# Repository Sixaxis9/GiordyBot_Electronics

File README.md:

# CNC-3Dprinter

In this repository I have uploaded all the material related to a fresh design of a machine capable of working various type of materials, including wood and aluminum, with the nice addition of an extruder to use it as a 3D printer.

I have uploaded the Eagle project of the board. Below you can find a list of all the important feautures and the distinctive sign of this board. I also have uploaded the Gerber files for printing a PCB, in case you would like to power your 3D printer or CNC with my hardware.

I also made a complete CAD model of this build, complete with FEM analysis in order to pick the best materials and optimize dimensions of the design. I will upload all those files in the nearest future.

A Wiki is available in the [apposite section](https://github.com/Sixaxis9/CNC-3Dprinter/wiki)

Below some pictures of the board:

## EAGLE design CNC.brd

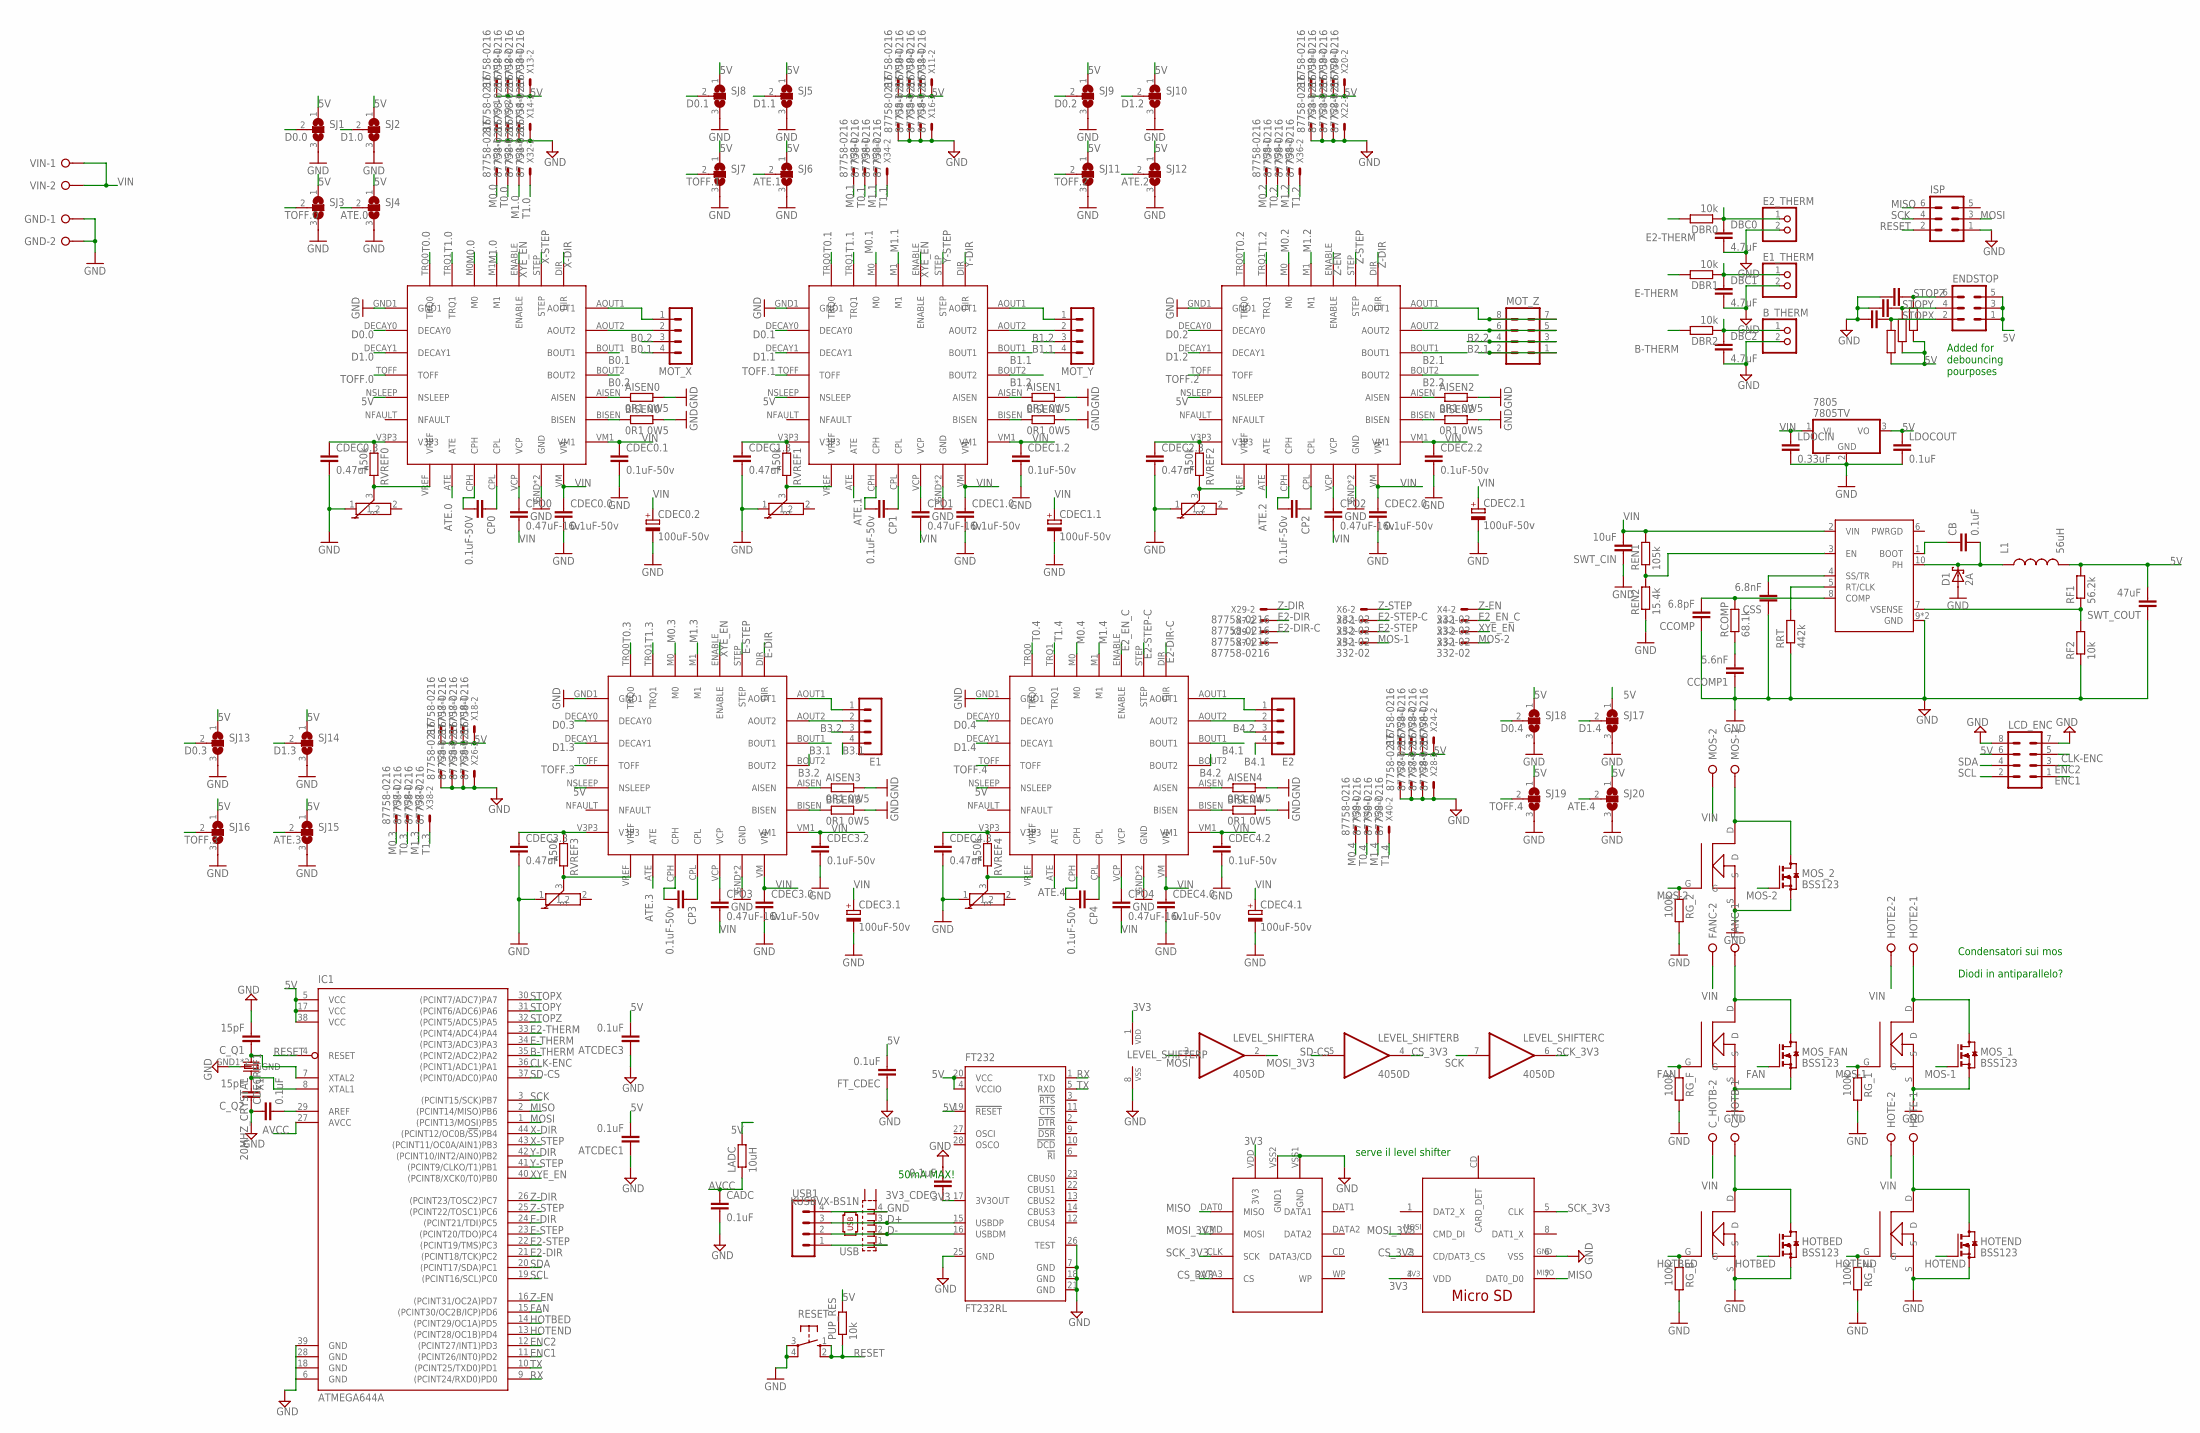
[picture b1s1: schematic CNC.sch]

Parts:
3V3_CDEC: 0.1uF; C0603
7805: 7805TV; TO220V
AISEN0, AISEN1, AISEN2, AISEN3, AISEN4: 0R1 0W5; R0805
ATCDEC1, ATCDEC3: 0.1uF; C0603
BISEN0, BISEN1, BISEN2, BISEN3, BISEN4: 0R1 0W5; R0805
B_THERM: PINHD-1X2; 1X02
CADC: 0.1uF; C0603
CB: 0.1uF; C0603
CCOMP: 6.8pF; C0603
CCOMP1: 5.6nF; C0603
CDEC0.0, CDEC0.1, CDEC1.0, CDEC1.2, CDEC2.0, CDEC2.2, CDEC3.0, CDEC3.2, CDEC4.0, CDEC4.2: 0.1uF-50v; C0603
CDEC0.2, CDEC1.1, CDEC2.1, CDEC3.1, CDEC4.1: 100uF-50v; E3,5-8
CDEC0.3, CDEC1.3, CDEC2.3, CDEC3.3, CDEC4.3: 0.47uF; C0603
CDECREF1: 0.1uF; C0603
CP0: 0.1uF-50V; C0603
CP1, CP2, CP3, CP4: 0.1uF-50v; C0603
CPO0, CPO1, CPO2, CPO3, CPO4: 0.47uF-16v; C0603
CSS: 6.8nF; C0603
C_HOTB: W237-02P; W237-132
C_Q1, C_Q2: 15pF; C0603
D1: 2A; SMB
DBC0, DBC1, DBC2: 4.7uF; C0603
DBC3, DBC4, DBC5: 0.1uF; C0603
DBR0, DBR1, DBR2, DBR3, DBR4, DBR5: 10k; R0603
E1, E2: MA04-1
E1_THERM, E2_THERM: PINHD-1X2; 1X02
ENDSTOP: MA03-2
EXT_1, EXT_2: DRV8880; HTSSOP
FANC: W237-02P; W237-132
FT232: FT232RL; SSOP28
FT_CDEC: 0.1uF; C0603
GND: W237-02P; W237-132
HOTBED: BSS123; SOT23
HOTBED1: POWER_MOSFET; D2PAK
HOTE, HOTE2: W237-02P; W237-132
HOTEND: BSS123; SOT23
HOTEND1: POWER_MOSFET; D2PAK
IC1: ATMEGA644A; TQFP44
ISP: MA03-2
L1: 56uH; INDUCTOR
LADC: 10uH; R0603
LCD_ENC: MA04-2
LDOCIN: 0.33uF; C0603
LDOCOUT: 0.1uF; C0603
LEVEL_SHIFTER: 4050D; SO16
MOS: W237-02P; W237-132
MOS11, MOS22: POWER_MOSFET; D2PAK
MOS_1, MOS_2: BSS123; SOT23
MOS_FAN: BSS123; SOT23
MOS_FAN1: POWER_MOSFET; D2PAK
MOT_X: MA04-1
MOT_Y: MA04-1
MOT_Z: MA04-2
PUP_RES: 10k; R0603
RCOMP: 68.1k; R0603
REN1: 105k; R0603
REN2: 15.4k; R0603
RESET: 10-XX; B3F-10XX
RF1: 56.2k; R0603
RF2: 10k; R0603
RG_1, RG_2: 100k; R0603
RG_B: 100k; R0603
RG_E: 100k; R0603
RG_F: 100k; R0603
RRT: 442k; R0603
RVREF0, RVREF1, RVREF2, RVREF3, RVREF4: 150k; R0603
SD: SD_CARD
SJ1, SJ2, SJ3, SJ4, SJ5, SJ6, SJ7, SJ8, SJ9, SJ10, SJ11, SJ12, SJ13, SJ14, SJ15, SJ16, SJ17, SJ18, SJ19, SJ20: SJ2W; SJ_2
SUPPLY: TPS54160; MSOP
SWT_CIN: 10uF; C0603
SWT_COUT: 47uF; C0603
T0: 100k; TRIMMER
T1, T2, T3, T4: TRIMMER
USB: KUSBVX-BS1N
USB1: MA04-1
USD: MICRO-SD
VIN: W237-02P; W237-132
X1: 20MHZ_CRYSTAL; SMD-3225_4P
X3, X4, X5, X6: 332-02
X7, X9, X10, X11, X12, X13, X14, X15, X16, X17, X18, X19, X20, X21, X22, X23, X24, X25, X26, X27, X28, X29, X31, X32, X33, X34, X35, X36, X37, X38, X39, X40: 87758-0216
X_AXIS: DRV8880; HTSSOP
Y-AXIS: DRV8880; HTSSOP
Z_AXIS: DRV8880; HTSSOP

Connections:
3V3: 3V3_CDEC.1, FT232.17 (3V3OUT), LEVEL_SHIFTER.1 (VDD), SD.VDD (3V3), USD.4 (VDD)
5V: 7805.3 (VO), ATCDEC1.2, ATCDEC3.2, DBR3.2, DBR4.2, DBR5.2, ENDSTOP.1, ENDSTOP.3, ENDSTOP.5, EXT_1.NSLEEP, EXT_2.NSLEEP, FT232.4 (VCCIO), FT232.19 (!RESET), FT232.20 (VCC), FT_CDEC.2, IC1.5 (VCC), IC1.17 (VCC), IC1.38 (VCC), L1.2, LADC.2, LCD_ENC.6, LDOCOUT.1, PUP_RES.2, RF1.2, SJ1.1, SJ2.1, SJ3.1, SJ4.1, SJ5.1, SJ6.1, SJ7.1, SJ8.1, SJ9.1, SJ10.1, SJ11.1, SJ12.1, SJ13.1, SJ14.1, SJ15.1, SJ16.1, SJ17.1, SJ18.1, SJ19.1, SJ20.1, SWT_COUT.2, X10.1, X10.2, X11.1, X11.2, X12.1, X12.2, X13.1, X13.2, X17.1, X17.2, X18.1, X18.2, X19.1, X19.2, X20.1, X20.2, X23.1, X23.2, X24.1, X24.2, X_AXIS.NSLEEP, Y-AXIS.NSLEEP, Z_AXIS.NSLEEP
ATE.0: SJ4.2, X_AXIS.ATE
ATE.1: SJ6.2, Y-AXIS.ATE
ATE.2: SJ12.2, Z_AXIS.ATE
ATE.3: EXT_1.ATE, SJ15.2
ATE.4: EXT_2.ATE, SJ20.2
AVCC: CADC.1, IC1.27 (AVCC), LADC.1
B0.1: MOT_X.4, X_AXIS.BOUT1
B0.2: MOT_X.3, X_AXIS.BOUT2
B1.1: MOT_Y.4, Y-AXIS.BOUT1
B1.2: MOT_Y.3, Y-AXIS.BOUT2
B2.1: MOT_Z.1, MOT_Z.2, Z_AXIS.BOUT1
B2.2: MOT_Z.3, MOT_Z.4, Z_AXIS.BOUT2
B3.1: E1.4, EXT_1.BOUT1
B3.2: E1.3, EXT_1.BOUT2
B4.1: E2.4, EXT_2.BOUT1
B4.2: E2.3, EXT_2.BOUT2
B-THERM: DBR2.2, IC1.35 ((PCINT2/ADC2)PA2)
CLK-ENC: IC1.36 ((PCINT1/ADC1)PA1), LCD_ENC.5
CS_3V3: LEVEL_SHIFTER.4 (O), SD.DATA3 (CS), USD.2 (CD/DAT3_CS)
D0.0: SJ1.2, X_AXIS.DECAY0
D0.1: SJ8.2, Y-AXIS.DECAY0
D0.2: SJ9.2, Z_AXIS.DECAY0
D0.3: EXT_1.DECAY0, SJ13.2
D0.4: EXT_2.DECAY0, SJ18.2
D1.0: SJ2.2, X_AXIS.DECAY1
D1.1: SJ5.2, Y-AXIS.DECAY1
D1.2: SJ10.2, Z_AXIS.DECAY1
D1.3: EXT_1.DECAY1, SJ14.2
D1.4: EXT_2.DECAY1, SJ17.2
D+: FT232.15 (USBDP), USB.3, USB1.3
D-: FT232.16 (USBDM), USB.2, USB1.2
E2-DIR: IC1.21 ((PCINT18/TCK)PC2), X7.2
E2-DIR-C: EXT_2.DIR, X29.1
E2-STEP: IC1.22 ((PCINT19/TMS)PC3), X5.2
E2-STEP-C: EXT_2.STEP, X6.1
E2-THERM: DBR0.2, IC1.33 ((PCINT4/ADC4)PA4)
E2_EN_C: EXT_2.ENABLE, X4.1
E-DIR: EXT_1.DIR, IC1.24 ((PCINT21/TDI)PC5)
E-STEP: EXT_1.STEP, IC1.23 ((PCINT20/TDO)PC4)
E-THERM: DBR1.2, IC1.34 ((PCINT3/ADC3)PA3)
ENC1: IC1.11 ((PCINT26/INT0)PD2), LCD_ENC.1
ENC2: IC1.12 ((PCINT27/INT1)PD3), LCD_ENC.3
FAN: IC1.15 ((PCINT30/OC2B/ICP)PD6), MOS_FAN.1 (G), MOS_FAN1.G, RG_F.1
GND: 3V3_CDEC.2, 7805.2 (GND), AISEN0.2, AISEN1.2, AISEN2.2, AISEN3.2, AISEN4.2, ATCDEC1.1, ATCDEC3.1, BISEN0.2, BISEN1.2, BISEN2.2, BISEN3.2, BISEN4.2, B_THERM.2, CADC.2, CCOMP.1, CCOMP1.1, CDEC0.0.2, CDEC0.1.2, CDEC0.2.-, CDEC0.3.2, CDEC1.0.2, CDEC1.1.-, CDEC1.2.2, CDEC1.3.2, CDEC2.0.2, CDEC2.1.-, CDEC2.2.2, CDEC2.3.2, CDEC3.0.2, CDEC3.1.-, CDEC3.2.2, CDEC3.3.2, CDEC4.0.2, CDEC4.1.-, CDEC4.2.2, CDEC4.3.2, CDECREF1.1, CSS.1, C_Q1.2, C_Q2.1, D1.A, DBC0.2, DBC1.2, DBC2.2, DBC3.2, DBC4.2, DBC5.2, E1_THERM.2, E2_THERM.2, EXT_1.GND, EXT_1.GND1, EXT_1.GND2 (GND), EXT_2.GND, EXT_2.GND1, EXT_2.GND2 (GND), FT232.7 (GND), FT232.18 (GND), FT232.21 (GND), FT232.25 (GND), FT232.26 (TEST), FT_CDEC.1, GND.1, GND.2, HOTBED.2 (S), HOTBED1.S, HOTEND.2 (S), HOTEND1.S, IC1.6 (GND), IC1.18 (GND), IC1.28 (GND), IC1.39 (GND), ISP.1, LCD_ENC.7, LCD_ENC.8, LDOCIN.2, LDOCOUT.2, LEVEL_SHIFTER.8 (VSS), MOS11.S, MOS22.S, MOS_1.2 (S), MOS_2.2 (S), MOS_FAN.2 (S), MOS_FAN1.S, REN2.1, RESET.3, RESET.4 (P1), RF2.1, RG_1.2, RG_2.2, RG_B.2, RG_E.2, RG_F.2, RRT.1, SD.VSS1 (GND), SD.VSS2 (GND1), SJ1.3, SJ2.3, SJ3.3, SJ4.3, SJ5.3, SJ6.3, SJ7.3, SJ8.3, SJ9.3, SJ10.3, SJ11.3, SJ12.3, SJ13.3, SJ14.3, SJ15.3, SJ16.3, SJ17.3, SJ18.3, SJ19.3, SJ20.3, SUPPLY.9 (GND), SUPPLY.GND, SWT_CIN.1, SWT_COUT.1, T0.1, T1.1, T2.1, T3.1, T4.1, USB.4, USB1.4, USD.6 (VSS), X1.GND1 (GND), X1.GND2 (GND), X9.1, X9.2, X14.1, X14.2, X15.1, X15.2, X16.1, X16.2, X21.1, X21.2, X22.1, X22.2, X25.1, X25.2, X26.1, X26.2, X27.1, X27.2, X28.1, X28.2, X_AXIS.GND, X_AXIS.GND1, X_AXIS.GND2 (GND), Y-AXIS.GND, Y-AXIS.GND1, Y-AXIS.GND2 (GND), Z_AXIS.GND, Z_AXIS.GND1, Z_AXIS.GND2 (GND)
HOTBED: HOTBED.1 (G), HOTBED1.G, IC1.14 ((PCINT29/OC1A)PD5), RG_B.1
HOTEND: HOTEND.1 (G), HOTEND1.G, IC1.13 ((PCINT28/OC1B)PD4), RG_E.1
M0.0: X31.1, X_AXIS.M0
M0.1: X33.1, Y-AXIS.M0
M0.2: X35.1, Z_AXIS.M0
M0.3: EXT_1.M0, X37.1
M0.4: EXT_2.M0, X39.1
M1.0: X31.2, X_AXIS.M1
M1.1: X33.2, Y-AXIS.M1
M1.2: X35.2, Z_AXIS.M1
M1.3: EXT_1.M1, X37.2
M1.4: EXT_2.M1, X39.2
MISO: IC1.2 ((PCINT14/MISO)PB6), ISP.6, SD.DAT0 (MISO), USD.7 (DAT0_D0)
MOS-1: MOS11.G, MOS_1.1 (G), RG_1.1, X5.1
MOS-2: MOS22.G, MOS_2.1 (G), RG_2.1, X3.1
MOSI: IC1.1 ((PCINT13/MOSI)PB5), ISP.3, LEVEL_SHIFTER.3 (I)
MOSI_3V3: LEVEL_SHIFTER.2 (O), SD.CMD (MOSI), USD.3 (CMD_DI)
unnamed: DBC1.1, DBR1.1, E1_THERM.1
unnamed: DBC0.1, DBR0.1, E2_THERM.1
unnamed: REN1.1, REN2.2, SUPPLY.3 (EN)
unnamed: USB.1, USB1.1
unnamed: MOT_Y.1, Y-AXIS.AOUT1
unnamed: MOT_Y.2, Y-AXIS.AOUT2
unnamed: MOT_X.1, X_AXIS.AOUT1
unnamed: MOT_X.2, X_AXIS.AOUT2
unnamed: MOT_Z.7, MOT_Z.8, Z_AXIS.AOUT1
unnamed: MOT_Z.5, MOT_Z.6, Z_AXIS.AOUT2
unnamed: E1.1, EXT_1.AOUT1
unnamed: E1.2, EXT_1.AOUT2
unnamed: E2.2, EXT_2.AOUT2
unnamed: E2.1, EXT_2.AOUT1
unnamed: RRT.2, SUPPLY.5 (RT/CLK)
unnamed: MOS.1, MOS22.D, MOS_2.3 (D)
unnamed: CDEC0.3.1, RVREF0.1, X_AXIS.V3P3
unnamed: CDEC1.3.1, RVREF1.1, Y-AXIS.V3P3
unnamed: CPO4.1, EXT_2.VCP
unnamed: CP4.1, EXT_2.CPL
unnamed: CP4.2, EXT_2.CPH
unnamed: CDEC2.3.1, RVREF2.1, Z_AXIS.V3P3
unnamed: CDEC4.3.1, EXT_2.V3P3, RVREF4.1
unnamed: CPO3.1, EXT_1.VCP
unnamed: CP3.1, EXT_1.CPL
unnamed: CP3.2, EXT_1.CPH
unnamed: CDEC3.3.1, EXT_1.V3P3, RVREF3.1
unnamed: CPO0.1, X_AXIS.VCP
unnamed: CP0.1, X_AXIS.CPL
unnamed: CP0.2, X_AXIS.CPH
unnamed: FANC.1, MOS_FAN.3 (D), MOS_FAN1.D
unnamed: HOTE2.1, MOS11.D, MOS_1.3 (D)
unnamed: CPO1.1, Y-AXIS.VCP
unnamed: CP1.1, Y-AXIS.CPL
unnamed: CP1.2, Y-AXIS.CPH
unnamed: HOTE.1, HOTEND.3 (D), HOTEND1.D
unnamed: CPO2.1, Z_AXIS.VCP
unnamed: CP2.1, Z_AXIS.CPL
unnamed: CP2.2, Z_AXIS.CPH
unnamed: C_HOTB.1, HOTBED.3 (D), HOTBED1.D
unnamed: C_Q1.1, IC1.7 (XTAL2), X1.X1
unnamed: C_Q2.2, IC1.8 (XTAL1), X1.X2
unnamed: CSS.2, SUPPLY.4 (SS/TR)
unnamed: CB.1, SUPPLY.1 (BOOT)
unnamed: CCOMP1.2, RCOMP.1
unnamed: AISEN1.1, Y-AXIS.AISEN
unnamed: BISEN1.1, Y-AXIS.BISEN
unnamed: AISEN2.1, Z_AXIS.AISEN
unnamed: BISEN2.1, Z_AXIS.BISEN
unnamed: AISEN3.1, EXT_1.AISEN
unnamed: BISEN3.1, EXT_1.BISEN
unnamed: AISEN4.1, EXT_2.AISEN
unnamed: BISEN4.1, EXT_2.BISEN
unnamed: AISEN0.1, X_AXIS.AISEN
unnamed: BISEN0.1, X_AXIS.BISEN
unnamed: EXT_2.VREF, RVREF4.2, T4.3
unnamed: EXT_1.VREF, RVREF3.2, T3.3
unnamed: RVREF0.2, T0.3, X_AXIS.VREF
unnamed: RVREF1.2, T1.3, Y-AXIS.VREF
unnamed: RVREF2.2, T2.3, Z_AXIS.VREF
unnamed: CCOMP.2, RCOMP.2, SUPPLY.8 (COMP)
unnamed: CDECREF1.2, IC1.29 (AREF)
unnamed: CB.2, D1.C, L1.1, SUPPLY.10 (PH)
unnamed: B_THERM.1, DBC2.1, DBR2.1
unnamed: RF1.1, RF2.2, SUPPLY.7 (VSENSE)
RESET: IC1.4 (RESET), ISP.2, PUP_RES.1, RESET.1 (S), RESET.2 (S1)
RX: FT232.1 (TXD), IC1.9 ((PCINT24/RXD0)PD0)
SCK: IC1.3 ((PCINT15/SCK)PB7), ISP.4, LEVEL_SHIFTER.7 (I)
SCK_3V3: LEVEL_SHIFTER.6 (O), SD.CLK (SCK), USD.5 (CLK)
SCL: IC1.19 ((PCINT16/SCL)PC0), LCD_ENC.2
SD-CS: IC1.37 ((PCINT0/ADC0)PA0), LEVEL_SHIFTER.5 (I)
SDA: IC1.20 ((PCINT17/SDA)PC1), LCD_ENC.4
STOPX: DBC3.1, DBR3.1, ENDSTOP.2, IC1.30 ((PCINT7/ADC7)PA7)
STOPY: DBC4.1, DBR4.1, ENDSTOP.4, IC1.31 ((PCINT6/ADC6)PA6)
STOPZ: DBC5.1, DBR5.1, ENDSTOP.6, IC1.32 ((PCINT5/ADC5)PA5)
T0.0: X32.1, X_AXIS.TRQ0
T0.1: X34.1, Y-AXIS.TRQ0
T0.2: X36.1, Z_AXIS.TRQ0
T0.3: EXT_1.TRQ0, X38.1
T0.4: EXT_2.TRQ0, X40.1
T1.0: X32.2, X_AXIS.TRQ1
T1.1: X34.2, Y-AXIS.TRQ1
T1.2: X36.2, Z_AXIS.TRQ1
T1.3: EXT_1.TRQ1, X38.2
T1.4: EXT_2.TRQ1, X40.2
TOFF.0: SJ3.2, X_AXIS.TOFF
TOFF.1: SJ7.2, Y-AXIS.TOFF
TOFF.2: SJ11.2, Z_AXIS.TOFF
TOFF.3: EXT_1.TOFF, SJ16.2
TOFF.4: EXT_2.TOFF, SJ19.2
TX: FT232.5 (RXD), IC1.10 ((PCINT25/TXD0)PD1)
VIN: 7805.1 (VI), CDEC0.0.1, CDEC0.1.1, CDEC0.2.+, CDEC1.0.1, CDEC1.1.+, CDEC1.2.1, CDEC2.0.1, CDEC2.1.+, CDEC2.2.1, CDEC3.0.1, CDEC3.1.+, CDEC3.2.1, CDEC4.0.1, CDEC4.1.+, CDEC4.2.1, CPO0.2, CPO1.2, CPO2.2, CPO3.2, CPO4.2, C_HOTB.2, EXT_1.VM, EXT_1.VM1, EXT_2.VM, EXT_2.VM1, FANC.2, HOTE.2, HOTE2.2, LDOCIN.1, MOS.2, REN1.2, SUPPLY.2 (VIN), SWT_CIN.2, VIN.1, VIN.2, X_AXIS.VM, X_AXIS.VM1, Y-AXIS.VM, Y-AXIS.VM1, Z_AXIS.VM, Z_AXIS.VM1
X-DIR: IC1.44 ((PCINT12/OC0B/!SS!)PB4), X_AXIS.DIR
X-STEP: IC1.43 ((PCINT11/OC0A/AIN1)PB3), X_AXIS.STEP
XYE_EN: EXT_1.ENABLE, IC1.40 ((PCINT8/XCK0/T0)PB0), X3.2, X_AXIS.ENABLE, Y-AXIS.ENABLE
Y-DIR: IC1.42 ((PCINT10/INT2/AIN0)PB2), Y-AXIS.DIR
Y-STEP: IC1.41 ((PCINT9/CLKO/T1)PB1), Y-AXIS.STEP
Z-DIR: IC1.26 ((PCINT23/TOSC2)PC7), X29.2, Z_AXIS.DIR
Z-EN: IC1.16 ((PCINT31/OC2A)PD7), X4.2, Z_AXIS.ENABLE
Z-STEP: IC1.25 ((PCINT22/TOSC1)PC6), X6.2, Z_AXIS.STEP

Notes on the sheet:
serve il level shifter
50mA MAX!
Added for debouncing pourposes
Condensatori sui mos
Diodi in antiparallelo?

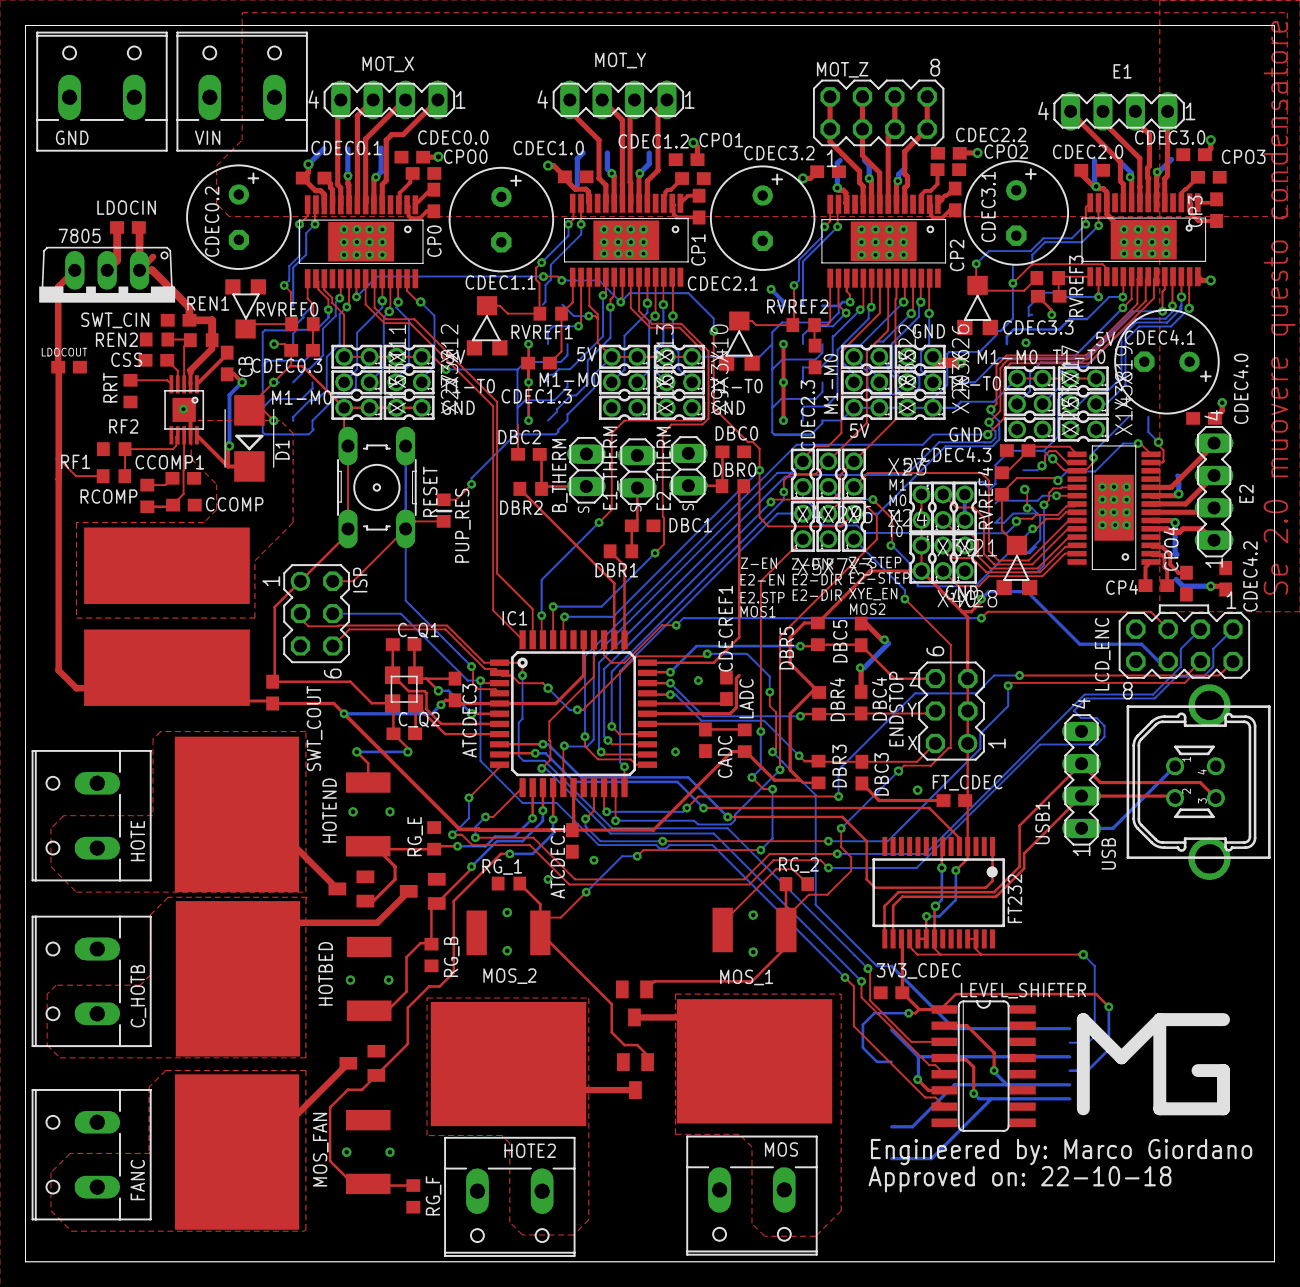
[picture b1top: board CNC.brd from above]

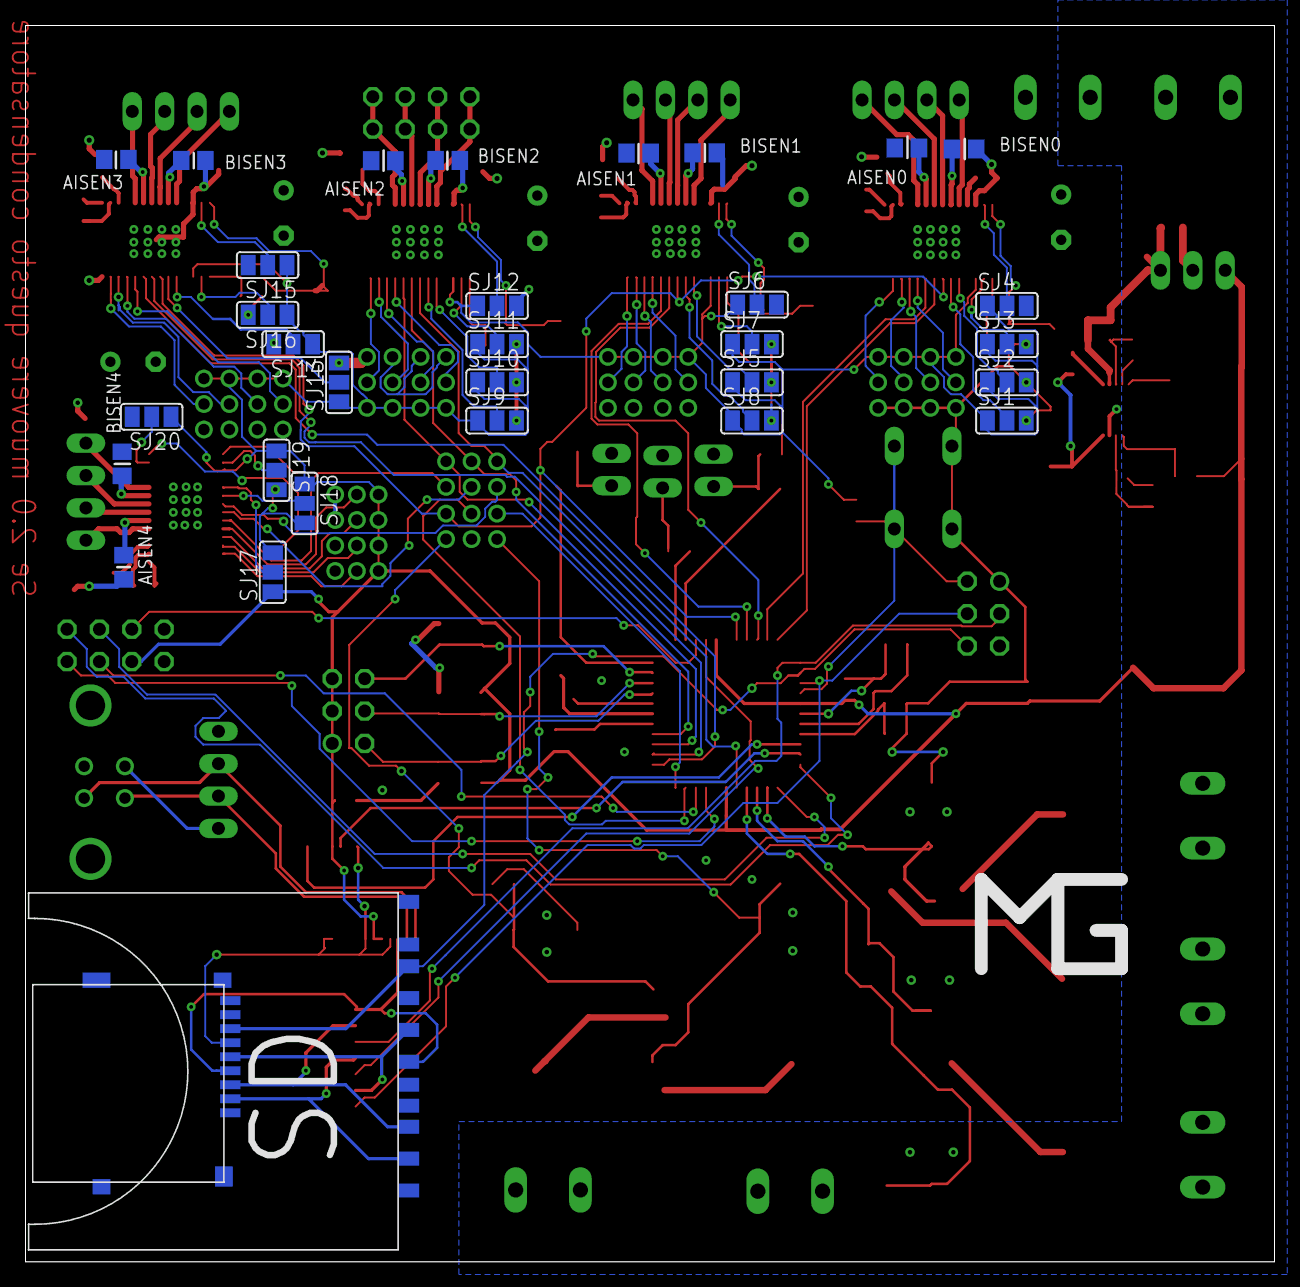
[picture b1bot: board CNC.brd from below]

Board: 2 copper layers, 98.0 x 97.0 mm, 193 parts (32 on the bottom side), 163 nets.

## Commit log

2019-01-07 Last version of PCB of my CNC&3D printer
    Last version of PCB of my CNC&3D printer is available! Huge modifications from previus versions, including a brand new stpper driver IC, provided by Texas Instruments DRV8880, with some amazin auto-t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
2019-01-07 Update images
2019-01-11 Refactor
2019-01-25 Added pictures
2019-01-25 Compressed image
2019-03-16 Addes side by side picture
2019-03-16 Modified PCB project picture
    Added a two pic side by side comparison
